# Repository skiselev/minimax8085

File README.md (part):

# MiniMax8085
Minimal 8085 Single Board Computer

## Table of Content
* [Introduction](#introduction)
* [Specifications](#specifications)
* [Hardware Documentation](#hardware-documentation)
  * [Schematic and PCB Layout](#schematic-and-pcb-layout)
  * [Design Description](#design-description)
  * [Jumpers and Connectors](#jumpers-and-connectors)
  * [Simple Programmable Logic Device](#simple-programmable-logic-device)
  * [Bill of Materials](#bill-of-materials)
* [Firmware and Software](#firmware-and-software)
  * [ROM Image](#rom-image)
  * [MON85 Monitor](#mon85-monitor)
  * [Tiny BASIC](#tiny-basic)
  * [IMSAI 8K BASIC](#imsai-8k-basic)
  * [Test Programs](#test-programs)
  * [Building the Software](#building-the-software)
* [3D Printable Enclosure](#3d-printable-enclosure)
* [Extension Boards](#extension-boards)
  * [Keypad and VFD Extension Board](#keypad-and-vfd-extension-board)
  * [Arithmetic and Extension Board](#arithmetic-and-extension-board)
* [Frequently Asked Questions and Troubleshooting](#frequently-asked-questions-and-troubleshooting)
* [References](#references)

## Introduction
The MiniMax8085 project has been brewing for almost three years. In the spring of 2014 my kids and I visited a local [surplus store](http://www.surplusgizmos.com/), where my kids found some Intel 8000 series parts in the kids-fill-your-bucket area. Among these ICs were there: an 8085 CPU, an 8155 RAM with I/O ports and timer, a couple of 8255 PPIs, an 8282 latch, and some 27C128 UV EPROMs. It looked like a good start for an 8085 based computer that can be used to teach my kids some computer design and programming basics.
I wanted the project to be simple to build, with a minimal number of components, but yet to be a fully functional single board computer (e.g. to include the memory and an input/output device, for example a UART) with an extension bus. I checked the Internet for existing homebrew 8085 computers and found Roman Fülek's [NCB85](http://archeocomp.blogspot.com/2013/01/ncb85.html) and [NCB85v2](http://archeocomp.blogspot.com/2014/01/ncb85-7-nove-ncb85v2.html) projects, and Glitch Works [8085 projects](http://www.glitchwrks.com/8085projects.html). While I liked these projects, they didn't quite meet my project design goals:
* [NCB85](http://archeocomp.blogspot.com/2013/01/ncb85.html) was the closest, but it doesn't have an extension bus
* [NCB85v2](http://archeocomp.blogspot.com/2014/01/ncb85-7-nove-ncb85v2.html) is a little bit too complicated for my needs
* [Glitch Works 8085](http://www.glitchwrks.com/8085projects.html) project didn't have an on-board UART

The resulting design includes 8085 CPU, 8251 USART, 32 KiB SRAM, 32 KiB or 16 KiB ROM. It uses a GAL16V8/ATF16V8 simple programmable logic device (SPLD) instead of discrete logic ICs for the address decode and the frequency divider for USART. It reduces the number of components, allows for tweaking the configuration by re-programming the SPLD, and provides an introduction to the programmable logic devices.

## Specifications
* 80C85A or 8085A CPU, 3.072 MHz, 4 MHz, 4.9152 MHz, 6.144 MHz, or 8 MHz CPU clock frequency
* 82C51A or 8251A USART for console connection
* 32 KiB of battery backed SRAM
* Up to 32 KiB of ROM. EEPROM, UV EPROM or Flash ROM memory is supported
* 40-pin extension bus connector, including most of 8085 signals and demultiplexed data and address buses

## Hardware Documentation

### Schematic and PCB Layout

[Schematic - Version 1.0](KiCad/Mini8085-Schematic-1.0.pdf)

[PCB Layout - Version 1.0](KiCad/Mini8085-Board-1.0.pdf)

### Design Description
The MiniMax8085 is based on the Intel 8085A CPU (U1). The 74*573 octal latch (U6) is used to demultiplex the lower 8-bit of address and data bus.
The board uses the Intel 8251A USART (U2) for serial input / output, for example for connecting a console. The MAX232A RS-232 driver/receiver (U7) is used to convert TTL logic levels to RS-232 voltage.
The 62256 32 KiB SRAM (U4) is used for the system RAM. The RAM is battery backed using the DS1210 NVRAM controller (U8).
The board supports a variety of ROM options (U3): The 28C256 EEPROM; UV EPROMs, such as 27C256 (32 KiB), 27C128 (16 KiB), and 27C64 (8 KiB); or The 29C256 Flash ROM ICs. Normally the ROM is mapped to the CPU memory beginning from the address *0x0000*, while the RAM is mapped beginning from the address *0x8000*. The ROM and RAM addresses can be swapped by pulling /SWAP_MEM signal low. This can be used, for example, to implement a CP/M extension card. 
The GAL16V8 simple programmable logic device (U5) implements all the required "glue" logic functions:
* Address decode and chip select for the USART. The default USART I/O address is *0x08*.
* Clock divider that divides the CPU clock to obtain USART transmit and receive clock. The divisor value depends on the CPU speed. Fuse maps with divide by 10 and 20, divide by 13 and 26, and divide by 16 and 32 ratios are provided to support common 8085A CPU clocks: 3.072 MHz, 4 MHz, 4.9152 MHz, 6.144 MHz, and 8 MHz.
* Address decode and chip select for the ROM and SRAM. The address decode logic include additional /SWAP_MEM input, which by default is configured to swap address mapping of ROM and RAM.

Please refer to the [Simple Programmable Logic Device](#simple-programmable-logic-device) section below for more details regarding the SPLD configuration and programming.

The MiniMax8085 includes a 40-pin extension connector (P4), that features the 8085A address and data buses, and control signals. Please refer to the Jumpers and Connectors section below for the connector pinout and signals description.

### Jumpers and Connectors

#### Jumpers JP1 and JP2 - ROM Configuration

These jumpers configure how pins 1 and 27 of the ROM IC (U3) are connected. The jumper settings are printed on the bottom side of the PCB.
ROM Type                   | Jumper JP1 Position - ROM Pin 1 Connection                        | JP2 Position - ROM Pin 27 Connection
-------------------------- | ----------------------------------------------------------------- | ------------------------------------
27C128, 27C64, 27128, 2764 | 2-3 - pin 1 connected to VCC                                      | 1-2 - pin 27 connected to VCC
27C256                     | 2-3 - pin 1 connected to VCC                                      | 2-JP1 pin 1 (jumper installed vertically), pin 27 connected to A14
28C256                     | 1-2 - pin 1 connected to A14                                      | 2-3 - pin 27 connected to /WR
29C256                     | 2-JP2 pin 3 (jumper installed vertically), pin 1 connected to /WR | 2-JP1 pin 1 (jumper installed vertically), pin 27 connected to A14

#### Jumper JP3 - USART Clock Frequency

JP3 sets the USART input clock frequency

Jumper Position | Crystal Y1 Frequency (CPU Frequency)                          | USART Clock Frequency | USART Bit rate
--------------- | ------------------------------------------------------------- | --------------------- | --------------
1-2             | 6.144 MHz (3.073 MHz), 8 MHz (4 MHz), 9.8304 MHz (4.9152 MHz) | 307.2 kHz             | 19200 bps (default) or 2400 bps, depending on USART configuration
1-2             | 12.288 MHz (6.144 MHz), 16 Mhz (8 MHz)                        | 614.4 kHz             | 38400 bps (default) or 4800 bps, depending on USART configuration
2-3             | 6.144 MHz (3.073 MHz), 8 MHz (4 MHz), 9.8304 MHz (4.9152 MHz) | 153.6 kHz             | 9600 bps (default) or 1200 bps, depending on USART configuration
2-3             | 12.288 MHz (6.144 MHz), 16 MHz (8 MHz)                        | 307.2 kHz             | 19200 bps (default) or 2400 bps, depending on USART configuration

#### Connector P1 - POWER

Connect regulated +5V power supply to this connector.
Pin                     | Description
----------------------- | -----------
tip (the inner contact) | Positive terminal - +5V
barrel / sleeve         | Negative terminal - ground

#### Connector P2 - SIO

Connector P2 contains the 8085A CPU serial input and output lines.
Pin | Description
--- | -----------
1   | Ground
2   | SOD / Serial Output Data
3   | SID / Serial Input Data

#### Connector P3 - SERIAL

P3 is the serial port connector. It is normally used for connecting a console or terminal. P3 uses pinout similar to that of IBM AT serial port (with some signals missing). Use a null modem cable to connect to a PC.

Pin Number | Signal Name       | Description and Notes
---------- | ----------------- | ---------------------
1          | DCD               | Carrier Detect; Not used - Not connected on the SBC
**2**      | **RX**            | **Receive Data; Input to SBC**
**3**      | **TX**            | **Transmit Data; Output from SBC**
4          | DTR               | Data Terminal Ready; Not used - Not connected on the SBC
**5**      | **Signal Ground** | **Connected to the SBC GND signal**
6          | DSR               | Data Set Ready; Not used - Not connected on the SBC
**7**      | **RTS**           | **Request to Send; Output from SBC**
**8**      | **CTS**           | **Clear to Send; Input to SBC**
9          | RI                | Ring Indicator; Not used - Not connected on the SBC
**Shield** | **DE9 Shield**    | **Connected to the SBC GND signal**

#### Connector P4 - EXTENSION

Connector P4 contains the 8085A CPU address and data buses, and control signals.

Pin | Signal    | Description                             | Pin | Signal | Description
--- | --------- | --------------------------------------- | --- | ------ | -----------
1   | TRAP      | Non-maskable interrupt input            | 21  | AD5    | Address/data bus - bit 5 bi-directional
2   | 3.073 MHz | CPU clock output                        | 22  | AD4    | Address/data bus - bit 4 bi-directional
3   | RST5_5    | RST5.5 interrupt input                  | 23  | AD7    | Address/data bus - bit 7 bi-directional
4   | INTR      | Interrupt request input                 | 24  | AD6    | Address/data bus - bit 6 bi-directional
5   | RST7_5    | RST7.5 interrupt input                  | 25  | /RD    | Read control output
6   | /INTA     | Interrupt acknowledge output            | 26  | IO/M   | I/O / memory cycle status output
7   | ALE	      | Address latch enable output             | 27  | /WR    | Write control output
8   | /SWAP_MEM | Swap ROM & RAM addresses input          | 28  | RESET  | Reset output
9   | A9        | Address bus - bit 9 output              | 29  | A1     | Address bus - bit 1 output
10  | A8        | Address bus - bit 8 output              | 30  | A0     | Address bus - bit 0 output
11  | A11       | Address bus - bit 11 output             | 31  | A3     | Address bus - bit 3 output
12  | A10       | Address bus - bit 10 output             | 32  | A2     | Address bus - bit 2 output
13  | A13       | Address bus - bit 13 output             | 33  | A5     | Address bus - bit 5 output
14  | A12       | Address bus - bit 12 output             | 34  | A4     | Address bus - bit 4 output
15  | A15       | Address bus - bit 15 output             | 35  | A7     | Address bus - bit 7 output
16  | A14       | Address bus - bit 14 output             | 36  | A6     | Address bus - bit 6 output
17  | AD1       | Address/data bus - bit 1 bi-directional | 37  | VCC    | Power - 5V
18  | AD0       | Address/data bus - bit 0 bi-directional | 38  | VCC    | Power - 5V
19  | AD3       | Address/data bus - bit 3 bi-directional | 39  | GND    | Power - Ground
20  | AD2       | Address/data bus - bit 2 bi-directional | 40  | GND    | Power - Ground

#### Connector P5 - VBAT

P5 is used to connect the battery for the SRAM backup. A 3-volt lithium cell, or 2-3 alkaline batteries connected in series can be used for this purpose.
Pin | Description
--- | -----------
1   | Battery voltage, 3V - 5V
2   | Ground

### Simple Programmable Logic Device

#### SPLD Files and Programming

As described above, the MiniMax8085 SBC uses a GAL16V8 simple programmable logic device (SPLD) to implement all the necessary glue logic. The SLPD sources and images (fuse maps are available [SPLD](SPLD/) folder of this GitHub repository:
* [Mini8085-3.072MHz.pld](SPLD/Mini8085-3.072MHz.pld) - SPLD source code for a system with CPU running on 3.072 MHz or 6.144 MHz clock frequency. 
  * [Mini8085-3.072MHz.jed](SPLD/Mini8085-3.072MHz.jed) - SPLD fuse map for a system with CPU running on 3.072 MHz or 6.144 MHz clock frequency
  * When used with 6.144 MHz CPU clock frequency, the USART clock will be doubled. So that it will work on 19200 bps instead of 9600 bps, or 38400 bps instead of 19200 bps, depending on [JP3 setting](#jumper-jp3---usart-clock-frequency)
* [Mini8085-3.9936MHz.pld](SPLD/Mini8085-3.9936MHz.pld) - SPLD source code for a system with CPU running on 3.9936 MHz (4 MHz) or 8 MHz clock frequency
  * [Mini8085-3.9936MHz.jed](SPLD/Mini8085-3.9936MHz.jed) - SPLD fuse map for a system with CPU running on 3.9936 MHz (4 MHz) or 8 MHz clock frequency
  * When used with 8 MHz CPU clock frequency, the USART clock will be doubled. So that it will work on 19200 bps instead of 9600 bps, or 38400 bps instead of 19200 bps, depending on [JP3 setting](#jumper-jp3---usart-clock-frequency)
* [Mini8085-4.9152MHz.pld](SPLD/Mini8085-4.9152MHz.pld) - SPLD source code for a system with CPU running on 4.9152 MHz clock frequency
  * [Mini8085-4.9152MHz.jed](SPLD/Mini8085-4.9152MHz.jed) - SPLD fuse map for a system with CPU running on 4.9152 MHz clock frequency

The SPLD IC has to be programmed using an EPROM programmer, such as a popular MiniPro TL866CS programmer. The process is very similar to programming regular EPROM ICs:
* Select IC manufacturer: Lattice for GAL16V8 or Atmel for ATF16V8
* Select the SPLD type: GAL16V8 or ATF16V8
* Load the SPLD fuse map - pick one of [Mini8085-3.072MHz.jed](SPLD/Mini8085-3.072MHz.jed), [Mini8085-3.9936MHz.jed](SPLD/Mini8085-3.9936MHz.jed), or [Mini8085-4.9152MHz.jed](SPLD/Mini8085-4.9152MHz.jed) files, depending on the CPU frequency (or the crystal resonator you are using).
* Program the SPLD. You might want to disable "lock" option, so that SPLD will remain readable after the programming.

#### SPLD Implementation
The [Mini8085-3.072MHz.pld](SPLD/Mini8085-3.072MHz.pld), [Mini8085-3.9936MHz.pld](SPLD/Mini8085-3.9936MHz.pld), and [Mini8085-4.9152MHz.pld](SPLD/Mini8085-4.9152MHz.pld) files contain the SPLD source code, that describes the logic equations defining the desired SPLD functionality. The source code can be divided into the following sections:

##### Header
This part contains the name of the SPLD and the project name:
<pre><code>
GAL16V8       ; 8085 SBC Logic first line : used GAL
8085Mini      ;                second line: any text (max. 8 char.)
</code></pre>

##### Pin Names Definition
This part assigns names to the SPLD pins. The names order corresponds to the pin numbers: the first line assigns names to the pins 1 - 10, and the second line to the pins 11 - 20. Note that several pins have fixed functions: pin 1 - Clock, pin 10 - GND, pin 11 - /OE, and pin 20 - VCC. Also pins 2 - 9 can be used as inputs only, while pins 12 - 19 can be used as either inputs or outputs.
<pre><code>
Clock IOM    A15    SWAPMEM A7    A6    A5    A4    A3   GND
/OE   RAMCS  ROMCS  USARTCS Q4    Q3    Q2    Q1    Q0   VCC
</code></pre>

##### Logic Equations - USART Clock Frequency Divider
The frequency divider is implemented as a synchronous counter, where all the outputs change their state simultaneously with the rising edge of the Clock signal. To achieve this, the SPLD is configured in *registered* mode (this is done automatically, by the SPLD assembler). In this mode the SPLD outputs with .R suffix (Q0.R - Q4.R) are configured as D flip-flops, and their logic equations describe the next state of the flip-flops (the values on their D inputs, that will be latched with the Clock signal). For example, in [Mini8085-4.9152MHz.pld](SPLD/Mini8085-4.9152MHz.pld) the next state of Q0 output is defined to be the inverse of its current state: Q0.R = /Q0. The Q0 - Q2 outputs are the outputs of intermediate stages of counter/divider, and they are not used in the MiniMax8085. The USART clock inputs are connected to either Q3 or Q4 output, depending on the position of the jumper JP3, resulting in divide by either 10 or 20 for 3.072 MHz CPU clock (using the [Mini8085-3.072MHz.pld](SPLD/Mini8085-3.072MHz.pld) fuse map), divide by either 13 or 26 for 4.9152 MHz CPU clock (using the [Mini8085-3.9936MHz.pld](SPLD/Mini8085-3.9936MHz.pld) fuse map), or divide by either 16 or 32 for 4.9152 MHz CPU clock (using the [Mini8085-4.9152MHz.pld](SPLD/Mini8085-4.9152MHz.pld) fuse map).

[Mini8085-4.9152MHz.pld](SPLD/Mini8085-4.9152MHz.pld): 5-bit binary counter, or divide by 32 frequency divider.
<pre><code>
Q0.R =   /Q0
 
Q1.R =    Q1 * /Q0
       + /Q1 *  Q0

Q2.R =    Q2 * /Q1
       +  Q2 * /Q0
       + /Q2 *  Q1 *  Q0

Q3.R =    Q3 * /Q2
       +  Q3 * /Q1
       +  Q3 * /Q0
       + /Q3 *  Q2 *  Q1 *  Q0

Q4.R =    Q4 * /Q3
       +  Q4 * /Q2
       +  Q4 * /Q1
       +  Q4 * /Q0
       + /Q4 *  Q3 *  Q2 *  Q1 *  Q0
</code></pre>

[Mini8085-3.072MHz.pld](SPLD/Mini8085-3.072MHz.pld): Q2-Q0 implement divide by 5 frequency divider, Q3 and Q4 stages divide the frequency further by 2 and 4 respectively.
<pre><code>
Q0.R =   /Q2 * /Q0

Q1.R =   /Q2 * /Q1 *  Q0
       + /Q2 *  Q1 * /Q0

Q2.R =   /Q2 *  Q1 *  Q0

Q3.R =    Q3 * /Q2
       + /Q3 *  Q2

Q4.R =    Q4 * /Q3
       +  Q4 * /Q2
       + /Q4 *  Q3 *  Q2
</code></pre>

#### Logic Equations - Memory Chip Select
These equations activate /ROMCS and /RAMCS signals:
The /ROMCS is active (LOW) when 8085 IO/M signal is LOW, indicating a memory access, and either A15 is LOW (lower 32 KiB of memory address space) and SWAPMEM is inactive (HIGH), or then A15 is HIGH (upper 32 KiB of memory address space), and SWAPMEM is active (LOW).
The /RAMCS is active (LOW) when 8085 IO/M is LOW, indicating a memory access, and either A15 is HIGH (upper 32 KiB of memory address space) and SWAPMEM is inactive (HIGH), or then A15 is LOW (lower 32 KiB of memory address space), and SWAPMEM is active (LOW).

<pre><code>
/ROMCS =   /IOM *  SWAPMEM * /A15
         + /IOM * /SWAPMEM *  A15

/RAMCS =   /IOM *  SWAPMEM *  A15
         + /IOM * /SWAPMEM * /A15
</code></pre>

#### Logic Equations - USART Chip Select
This equation activates the /USARTCS signal. It is active (LOW) when 8085 IO/M signal is HIGH, indicating an I/O port access, address lines A7-A4 are LOW, and address line A3 is high. So that USART is selected using  00001xxxb addresses (8h-0Fh).

<pre><code>
/USARTCS = IOM * /A7 * /A6 * /A5 * /A4 * A3
</code></pre>

### Bill of Materials

[MiniMax8085 project on Mouser.com](http://www.mouser.com/ProjectManager/ProjectDetail.aspx?AccessID=e60fdda470) - View and order all components except of the 8085A CPU, the 8251A USART, and the PCB.

[MiniMax8085 project on OSHPark.com](https://www.oshpark.com/shared_projects/CyQsELdX) - View and order the MiniMax8085 PCB.

Component Type | Reference | Description                               | Quantity | Possible Sources and Notes
-------------- | --------- | ----------------------------------------- | -------- | --------------------------
PCB            |           | MiniMax8085 PCB Version 1.0               | 1        | OSH Park [MiniMax 8085 V1.0](https://www.oshpark.com/shared_projects/CyQsELdX)
Capacitor      | C1 - C11  | 0.1 uF ceramic, 5.08 mm lead spacing      | 11       | Mouser [594-K104K15X7RF53H5](https://www.mouser.com/ProductDetail/594-K104K15X7RF53H5), [810-FG28X7R1H104KNT6](https://www.mouser.com/ProductDetail/810-FG28X7R1H104KNT6); Jameco [15270](https://www.jameco.com/z/DC-1-50-7-Jameco-Valuepro-Capacitor-Ceramic-Disc-0-1-micro-F-50V-plusmn-20-_15270.html)
Capacitor      | C12       | 1 uF ceramic, 5.08 mm lead spacing        | 1        | Mouser [810-FG28X7R1E105KRT6](https://www.mouser.com/ProductDetail/810-FG28X7R1E105KRT6)
Capacitor      | C13       | 10 uF ceramic, 5.08 mm lead spacing       | 1        | Mouser [810-FG28X5R1E106MR00](https://www.mouser.com/ProductDetail/810-FG28X5R1E106MR00). Note: Can be replaced with tantalum or electrolytic capacitors
Capacitor      | C14, C15  | 33 pF ceramic, 5.08 mm lead spacing       | 2        | Mouser [75-1C20C0G330J050B](https://www.mouser.com/ProductDetail/75-1C20C0G330J050B); Jameco [332217](https://www.jameco.com/z/DC33-50-Jameco-Valuepro-Capacitor-Ceramic-Disc-33pF-50V-plusmn20-37_332217.html).Note: Install only when using CMOS 80C85A CPU. Do not install when using NMOS 8085A
Connector      | P1        | DC jack                                   | 1        | Mouser [806-KLDX-0202-A](https://www.mouser.com/ProductDetail/806-KLDX-0202-A); Jameco [101179](https://www.jameco.com/z/GCD014-R-Jameco-Valuepro-2-1mm-Male-DC-Power-Jack-Solder-Eyelet-Terminals_101179.html), [101178](https://www.jameco.com/z/GCD014-Jameco-Valuepro-2-1mm-DC-Power-Jack-Male-Solder-Eyelet-Panel-Mount-Groove-_101178.html)
Connector      | P2, JP1 - JP3 | 3x1 pin header                        | 4        | Mouser [855-M20-9990345](https://www.mouser.com/ProductDetail/855-M20-9990345), [649-69190-103HLF](https://www.mouser.com/ProductDetail/649-69190-103HLF), [649-78229-103HLF](https://www.mouser.com/ProductDetail/649-78229-103HLF); Jameco [109576](https://www.jameco.com/z/7000-1X3SG-R-Jameco-Valuepro-Header-1-Straight-Male-1-Row-3-Pin-10-025-Post-23-Goldtail_109576.html)
Connector      | P3        | DE9M, right angle PCB mount               | 1        | Mouser [806-K22X-E9P-N-99](https://www.mouser.com/ProductDetail/806-K22X-E9P-N-99) (teal color), [806-K22X-E9P-N](https://www.mouser.com/ProductDetail/806-K22X-E9P-N); Jameco [104943](https://www.jameco.com/z/1008-9P-R-Jameco-Valuepro-Connector-D-Subminiature-Male-9-Position-2-77mm-Solder-Right-Angle-Through-Hole-9-Terminal-1-Port_104943.html), [614459](https://www.jameco.com/z/747840-6-TE-Connectivity-Connector-D-Subminiature-Plug-9-Position-2-74mm-Solder-Right-Angle-Through-Hole-9-Terminal-1-Port-Tray_614459.html), [614432](https://www.jameco.com/z/5747840-3-TE-Connectivity-Connector-D-Subminiature-Plug-9-Position-2-74mm-Solder-Right-Angle-Through-Hole-9-Terminal-1-Port_960837.html)
Connector      | P4        | 20x2 pin socket                           | 1        | Mouser [517-929852-01-20-RB](https://www.mouser.com/ProductDetail/517-929852-01-20-RB). Note: Optional, used for extension bus
Connector      | P5        | 2 pin header with friction lock           | 1        | Mouser [571-6404562](https://www.mouser.com/ProductDetail/571-6404562), [571-3-641126-2](https://www.mouser.com/ProductDetail/571-3-641126-2), [571-3-641215-2](https://www.mouser.com/ProductDetail/571-3-641215-2); Jameco [232266](https://www.jameco.com/z/22-23-2021-Molex-Connector-Wire-to-Board-Header-2-Position-2-54mm-Solder-Straight-Thru-Hole-Color-may-vary-_232266.html), [613931](https://www.jameco.com/z/640456-2-TE-Connectivity-Connector-Wire-to-Board-Header-2-Position-2-54mm-Solder-Straight-Thru-Hole_613931.html). Note: Optional, used for SRAM battery backup. Corresponding female connector: Mouser [571-13758202](https://www.mouser.com/ProductDetail/571-13758202); Jameco [234798](https://www.jameco.com/z/22-01-3027-Molex-Straight-Connector-Housing-Receptacle-2-Position-2-54mm-Color-may-vary-_234798.html). Contacts (2 contacts needed): Mouser [571-14453361](https://www.mouser.com/ProductDetail/571-14453361); Jameco [234923](https://www.jameco.com/z/08-50-0114-Molex-0-100-2-54mm-Connector-Contact-Female-1-Position-Crimp-Straight-Cable-Mount-Bag_234923.html), [736501](https://www.jameco.com/z/08-50-0113-Molex-Connector-Contact-Female-1-Position-Crimp-Straight-Cable-Mount-Reel_736501.html).  It is recommended to use a polarized header to avoid incorrect power polarity.
Diode          | D1        | 1N4148                                    | 1        | Mouser [512-1N4148TR](https://www.mouser.com/ProductDetail/512-1N4148TR), [512-1N4148](https://www.mouser.com/ProductDetail/512-1N4148), [78-1N4148](https://www.mouser.com/ProductDetail/78-1N4148); Jameco [36038](https://www.jameco.com/z/1N4148-Major-Brands-Diode-1N4148-100V-200mA-10mA-If-Small-Signal-Switching-Bulk-_36038.html), [179215](https://www.jameco.com/z/1N4148-Major-Brands-Diode-1N4148-100V-200mA-10mA-If-Small-Signal-Switching-Bulk-_36038.html)
LED            | D2        | LED Indicator, Dialight 566-0206F         | 1        | Mouser [645-566-0206F](https://www.mouser.com/ProductDetail/645-566-0206F).  Note: Can be replaced with a standard 3 mm or 5 mm LED
Resistor       | R1        | 33 Ohm, 1/4 W                             | 1        | Mouser [240-CFR-25JT-52-33R](https://www.mouser.com/ProductDetail/240-CFR-25JT-52-33R); Jameco [690507](https://www.jameco.com/z/CF1-4W330JRC-Jameco-Valuepro-Resistor-Carbon-Film-33-Ohm-5-1-4-Watt_690507.html)
Resistor       | R2        | 470 Ohm, 1/4 W                            | 1        | Mouser [603-CFR-25JT-52-470R](https://www.mouser.com/ProductDetail/603-CFR-25JT-52-470R); Jameco [690785](https://www.jameco.com/z/CF1-4W471JRC-Jameco-Valuepro-Resistor-Carbon-Film-470-Ohm-1-4-Watt-5-_690785.html)
Resistor       | R3        | 100 kOhm, 1/4 W                           | 1        | Mouser [603-CFR-25JT-52-100K](https://www.mouser.com/ProductDetail/603-CFR-25JT-52-100K); Jameco [691340](https://www.jameco.com/z/CF1-4W104JRC-Jameco-Valuepro-Resistor-Carbon-Film-100k-Ohm-1-4-Watt-5-_691340.html)
Resistor Array | RR1, RR2  | 4.7 kOhm, 6 pin, bussed resistor array    | 2        | Mouser [264-4.7K-RC](https://www.mouser.com/ProductDetail/264-4.7K-RC), [652-4606X-1LF-4.7K](https://www.mouser.com/ProductDetail/652-4606X-1LF-4.7K)
Switch         | SW1       | Tactile switch, right angle               | 1        | Mouser [653-B3F-3100](https://www.mouser.com/ProductDetail/653-B3F-3100), [653-B3F-3152](https://www.mouser.com/ProductDetail/653-B3F-3152), [706-95C06A2RAT](https://www.mouser.com/ProductDetail/706-95C06A2RAT), [706-95C06C2RAT](https://www.mouser.com/ProductDetail/706-95C06C2RAT), [706-95C06F2RAT](https://www.mouser.com/ProductDetail/706-95C06F2RAT); Jameco [2280495](https://www.jameco.com/z/SKHHLNA010-Alps-Electric-SPST-NO-OFF-MOM-Tactile-Switch-12VDC-50mA_2280495.html). Note: Switches can have different actuator length. You might want to select the switch according your own preferences, for example the enclosure type you want to use, and whatever you want the reset button to stick out of the enclosure or to stay hidden inside.
Crystal        | Y1        | 6.144 MHz quartz resonator for 3 MHz CPU; 8 MHz quartz resonator for 4 MHz CPU; 9.8304 MHz quartz resonator for 5 MHz CPU; 12.288 MHz quartz resonator for 6 MHz CPU ; 16 MHz quartz resonator for 8 MHz CPU | 1 | Mouser [520-61-18-4XEN](https://www.mouser.com/ProductDetail/520-61-18-4XEN) (6.144 MHz), [695-HC49US-983-U](https://www.mouser.com/ProductDetail/695-HC49US-983-U) (9.8304 MHz), [695-HC49US-122-U](https://www.mouser.com/ProductDetail/695-HC49US-122-U) (12.288 MHz), [815-ABL-16-B2](https://www.mouser.com/ProductDetail/815-ABL-16-B2) (16 MHz); Unicorn Electronics 6.144 MHz or 9.8304 MHz according to desired CPU clock frequency.
IC             | U1        | 80C85A, 8085A-2, or 8085A CPU             | 1        | Jameco [8085A-2, 5 MHz - 52071](https://www.jameco.com/z/8085A-2-Major-Brands-IC-8085A-2-8-Bit-CPU-32-I-O-5MHz-DIP-40-pin_52071.html), [8085A, 3 MHz - 52062](https://www.jameco.com/z/8085A-Major-Brands-IC-8085A-8-Bit-HMOS-MPU_52062.html); Unicorn Electronics 80C85, 8085A-2, or 8085A; eBay (search for 80C85 or 8085 CPUs, or IM1821VM85A / ИМ1821ВМ85А for Soviet 80C85 clone).  Note: Use CMOS part - 80C85A for lower power consumption
IC             | U2        | 82C51A, or 8251A USART                    | 1        | Jameco [8251A - 52652](https://www.jameco.com/z/8251A-Major-Brands-IC-8251A-USART-28-pin-DIP_52652.html) [82C51A - 52370](https://www.jameco.com/z/82C51A-Major-Brands-IC-82C51A-USART-CMOS-Transceiver-28-pin-DIP_52370.html), [NEC D8251AC - 52644](https://www.jameco.com/z/D8251AC-NEC-Corporation-IC-USART-8251-Dip-28_52644.html); Unicorn Electronics 82C51 or 8051; eBay (search for 82C51 or 8251 USART, or 580VV51 / 580ВВ51 for Soviet 8251 clone).  Note: Use CMOS part - 82C51A for lower power consumption
IC             | U3        | 28C256 EEPROM, 27C256 UV EPROM, 27C128 UV EPROM, 27128 UV EPROM, 27C64 UV EPROM, 2764 UV EPROM | 1 | Mouser [556-AT28C25615PU](https://www.mouser.com/ProductDetail/556-AT28C25615PU); Jameco [28C256 EEPROM - 74843](https://www.jameco.com/z/28C256-15-Major-Brands-IC-28C256-15-EEPROM-256K-Bit-CMOS-Parallel_74843.html), [27C256 UV EPROM - 39714](https://www.jameco.com/z/27C256-15-Major-Brands-IC-27C256-15-EPROM-256K-Bit-150ns-CMOS-UV-Erasable-Prommable-ROM_39714.html); Unicorn Electronics 28C256-15 (EEPROM), 27C256 or 27C128 (UV EPROM). Note: EEPROM parts are recommended. UV lamp is required to erase UV EPROMs
IC             | U4        | 62256 SRAM                                | 1        | Mouser [913-AS6C62256-55PCN](https://www.mouser.com/ProductDetail/913-AS6C62256-55PCN); Jameco [CY62256LL-70PC - 391822](https://www.jameco.com/z/CY62256LL-70PC-Cypress-Semiconductor-IC-CY62256LL-70PC-CMOS-SRAM-256k-Bit-32kx8-Asynch-70ns-Low-Power_391822.html), [CY62256L-70PC - 391793](https://www.jameco.com/z/CY62256L-70PC-Cypress-Semiconductor-IC-CY62256L-70PC-CMOS-SRAM-256K-Bit-32kx8-55-70ns-Low-Power_391793.html), [62256LP-70 - 82472](https://www.jameco.com/z/62256LP-70-Major-Brands-IC-62256LP-CMOS-SRAM-256K-Bit-32Kx8-70ns-Low-Power_82472.html), [62256LP-10 - 42833](https://www.jameco.com/z/62256LP-10-Major-Brands-Static-RAM-32K-x-8-Bit-High-Speed-CMOS-100ns-DIP-28_42833.html), [62256LP-15 - 42850](https://www.jameco.com/z/62256LP-15-Major-Brands-Static-RAM-32K-x-8-Bit-High-Speed-CMOS-150ns-DIP-28_42850.html); Unicorn Electronics 62256LP-70 (or any other 62256)
IC             | U5        | GAL16V8, ATF16V8                          | 1        | Mouser [556-AF16V8B15PU](https://www.mouser.com/ProductDetail/556-AF16V8B15PU), Jameco [GAL16V8D-15LP - 2290551](https://www.jameco.com/z/GAL16V8D-15LP-Lattice-Semiconductor-Corporation-IC-16V8D-15-High-Performance-EE-CMOS-PLD-Generic-Array-Logic-15ns-90mA-250MHz_2290551.html), [GAL16V8D-25LP - 876539](https://www.jameco.com/z/GAL16V8D-25LP-Lattice-Semiconductor-Corporation-IC-GAL16V8D-25-EECMOS-64x32-GAL-41-6MHz-20-pin-DIP_876539.html); Unicorn Electronics 16V8 (10 ns, 12 ns, or 15 ns versions would work. Make sure to contact the seller and ask specifically for Lattice GAL16V8 part. iCT PEEL16V8 parts are not supported by MiniPro TL866CS programmer)
IC             | U6        | 74HCT573, 74ALS573, 74F573                | 1        | Mouser [595-SN74HCT573N](https://www.mouser.com/ProductDetail/595-SN74HCT573N), [595-SN74AHCT573N](https://www.mouser.com/ProductDetail/595-SN74AHCT573N), [595-SN74F573N](https://www.mouser.com/ProductDetail/595-SN74F573N), [595-SN74ALS573CN](https://www.mouser.com/ProductDetail/595-SN74ALS573CN); Jameco [74HCT573 - 45090](https://www.jameco.com/z/74HCT573-Major-Brands-IC-74HCT573-Tri-State-Octal-D-type-Transparent-Latch_45090.html); Unicorn Electronics 74HCT573, 74F573, 74ALS573; eBay (search for 74HCT573, 74ALS573, 74F573, or KR1533IR33 / КР1533ИР33 for Soviet 74ALS573 clone)
IC             | U7        | MAX202,  MAX232A                          | 1        | Mouser [595-TRS202ECN](https://www.mouser.com/ProductDetail/595-TRS202ECN), [700-MAX202CPE](https://www.mouser.com/ProductDetail/700-MAX202CPE), [700-MAX232ACPE](https://www.mouser.com/ProductDetail/700-MAX232ACPE); Jameco [MAX202CPE - 142535](https://www.jameco.com/z/MAX202CPE-Major-Brands-IC-MAX202CPE-RS-232-Line-Transceiver-16-pin-DIP_142535.html); Unicorn Electronics MAX202
IC             | U8        | Maxim DS1210, or Maxim MXD1210            | 1        | Mouser [700-MXD1210CPA](https://www.mouser.com/ProductDetail/700-MXD1210CPA); Jameco [DS1210 - 114198](https://www.jameco.com/z/DS1210-Dallas-Semiconductor-IC-DS1210-Nonvolatile-Controller-8-pin-DIP_114198.html); Unicorn Electronics DS1210. Note: Optional, used for SRAM battery backup. If not populated - install two wire jumpers instead as shown on the PCB silk screen
IC Socket      | U1        | 40 pin 600 mil DIP socket                 | 1        | Mouser [517-4840-6000-CP](https://www.mouser.com/ProductDetail/517-4840-6000-CP), [649-DILB40P223TLF](https://www.mouser.com/ProductDetail/649-DILB40P223TLF); Jameco [41111](https://www.jameco.com/z/6000-40DW-R-Jameco-Valuepro-40-Pin-Dual-Wipe-Low-Profile-IC-Socket-0-60-Inch-Wide_112311.html)
IC Socket      | U2 - U4   | 28 pin 600 mil DIP socket                 | 3        | Mouser [517-4828-6000-CP](https://www.mouser.com/ProductDetail/517-4828-6000-CP), [649-DILB28P223TLF](https://www.mouser.com/ProductDetail/649-DILB28P223TLF); Jameco [40301](https://www.jameco.com/z/28LPD-6-Jameco-Valuepro-28-Pin-Dual-Wipe-Low-Profile-IC-Socket-0-6-Inch-Wide_40301.html)
IC Socket      | U5, U6    | 20 pin 300 mil DIP socket                 | 2        | Mouser [517-4820-3000-CP](https://www.mouser.com/ProductDetail/517-4820-3000-CP), [649-DILB20P-223TLF](https://www.mouser.com/ProductDetail/649-DILB20P-223TLF); Jameco [38608](https://www.jameco.com/z/20LPD-Major-Brands-20-Pin-0-3-Inch-Wide-Low-Profile-Dual-Wipe-IC-Socket_112248.html)
IC Socket      | U7        | 16 pin 300 mil DIP socket                 | 1        | Mouser [517-4816-3000-CP](https://www.mouser.com/ProductDetail/517-4816-3000-CP), [649-DILB16P-223TLF](https://www.mouser.com/ProductDetail/649-DILB16P-223TLF); Jameco [37373](https://www.jameco.com/z/ICS-316-T-Jameco-Valuepro-IC-Socket-16-Pin-Dual-Wipe-Low-Profile-0-3-Inch-Wide_112222.html)
IC Socket      | U8        | 8 pin 300 mil DIP socket                  | 1        | Mouser [517-4808-3000-CP](https://www.mouser.com/ProductDetail/517-4808-3000-CP), [649-DILB8P223TLF](https://www.mouser.com/ProductDetail/649-DILB8P223TLF); Jameco [112206](https://www.jameco.com/z/8LPD-Jameco-Valuepro-8-Pin-IC-Socket-Dual-Wipe-Low-Profile-0-30-Inch-Wide_112206.html)

#### Replacement Notes

* CMOS parts are preferred for lower power consumption.
* 80C85 (CPU) - Any type in DIP-40 package will do. Use 6.144 MHz crystal for 3 MHz parts. Such parts usually don't have any numeric suffix in the part name. For example Intel P8085AH is a 3 MHz part, while Intel P8085AH-2 is a 5 MHz part.
  * CMOS parts: MSM80C85A or M80C85A (OKI), CA80C85B (Calmos, Tundra), IM1821VM85A (Soviet/Russian Clone)
  * NMOS parts: P8085A (Intel, AMD), P8085AH, P8085AH-2, P8085AH-1 (Intel, newer HMOS process, 3 MHz, 5 MHz, and 6 MHz parts respectively), M5L8085AP (Mitsubishi), TMP8085AP (Toshiba), and so on.
* 80C51A (USART) - Any type in DIP-28 package.
* 28C256 (EEPROM, EPROM) - The board support a wide variety of ROMs. Note that JP1 and JP2 jumpers need to be set according to the ROM type.
  * 28C256 EEPROM: Atmel/Microchip AT28C256, Xicor X28C256
  * CMOS UV EPROMs: 27C256 UV EPROMs (32 KiB), 27C128 UV EPROMs (16 KiB), 27C64 UV EPROMs (8 KiB)
  * NMOS UV EPROMs: 27256 UV EPROMs (32 KiB), 27128 UV EPROMs (16 KiB), 2764 UV EPROMs (8 KiB)
  * 62256-like NVRAM (32 KiB)
  * AT29C256 Flash ROM
* 62256 (SRAM) - A low-power CMOS SRAM 32KiB, in DIP-28 wide (600 mils) packages. Here are some common parts:
  * In production: AS6C62256 (Alliance Memory), CY62256N (Cypress)
  * Old stock: HM62256LP (Hitachi), HY62256 (Hyundai), KM62256 (Samsung), UM62256 (UMC)
* GAL16V8 (SPLD): Needs to be in DIP-20 package
  * In production:  Atmel/Microchip ATF16V8
  * Old stock: Lattice GAL16V8 (any modification)
  * iCT PEEL16V8 might work, but it is not supported by common MiniPro TL866CS programmer
* 74HC573 (Octal D Latch with 3-STATE Outputs) - Can be replaced with any 74-series family that works with 5V power supply voltage. 
  * CMOS parts: 74HC573, 74ACT573, 74HCT573, 74AHCT573, 74AC573, 74ACT573
  * TTL parts: 74ALS573, 74F573, 74LS573
* MAX232A (RS-232 Drivers/Receivers) - There is a variety of compatible ICs available from various manufacturers. Note that the original MAX232 part as well as some compatible ICs require 1 uF capacitors for charge pumps (C7-C11).
  * Maxim: MAX232A, MAX202, MAX232
  * Texas Instruments: TRS202, MAX232
  * Exar: SP232
  * Analog Devices: ADM202, ADM232
  * Intersil: HIN202, HIN232
* LED D2 - Can be replaced by a 3 mm LED with pins bent at 90 degrees.

## Firmware and Software

### ROM Image

The pre-built [ROM image](software/mon85-tinybasic-8kbasic.bin) for MiniMax8085 containing, the MON85 monitor, Tiny BASIC, and IMSAI 8K BASIC is provided in this repository.
This ROM image has the following layout:
* 0x0000 - 0x0FFF - MON85 Monitor. It will run automatically upon power-on or reset
* 0x1000 - 0x17FF - Tiny BASIC. Use MON85 **G 1000** command to run it
* 0x1800 - 0x3FFF - IMSAI 8K BASIC. Use MON85 **G 1800** command to run it
The image size is 8 KiB, and it will work with either 16 KiB EPROMs (e.g. 27128), and 32 KiB EPROMs. It can be programmed into 8 KiB EPROM, leaving out the IMSAI 8K BASIC.

### MON85 Monitor

MiniMax8085 uses MON85 Software Debug Monitor For the 8085/8080 written by Dave Dunfield. Specifically it was tested with the improved by Roman Borik [version 1.2](http://blog.borik.net/2012/01/upraveny-monitor-pre-ncb85.html). This version adds support for undocumented 8085 instructions and flags.

#### Usage Notes
* Use *?* command to get a short summary of the MON85 commands
* Press *ESC* button to interrupt currently running command and return to the command prompt
* Addresses and data are typed in hexadecimal, without any preferences. For example *M 18F0*

#### Files

* [MON85 source code modified for MiniMax8085](software/mon85/mon85-mini85.asm)
* [MON85 V1.2 source](software/mon85/mon85-v12-ncb85.asm)
* [MON85 Documentation](software/mon85/mon85.txt)

### Tiny BASIC

The famous [Tiny BASIC](https://en.wikipedia.org/wiki/Tiny_BASIC) 2.0 written by Li-Chen Wang and modified by Roger Rauskolb, runs on MiniMax8085 with very little modifications: The 8251 USART I/O address needs to be updated, and its initialization parameters need to be slightly updated to use 1 stop bit instead of two, and to enable CTS/RTS flow control. Also the RAM addresses need to be updated to start from 8000h.

#### Files

* [Tiny BASIC source code modified for MiniMax8085](software/tinybasic/tinybasic-2.0-mini85.asm)
* [Tiny BASIC source code modified for AS Macro Assembler](software/tinybasic/tinybasic-2.0.asm)
* [Tiny BASIC article - Interface Age Magazine, December 1976](software/tinybasic/TinyBASIC-2.0.pdf)

### IMSAI 8K BASIC

IMSAI 8K BASIC runs on MiniMax8085 with minimal modifications (memory and USART I/O addresses), and provides floating point support. With that being said, it is slower that Tiny BASIC.

#### Usage Notes
* The operators and commands must be typed in upper case
* After power-on, make sure to type *NEW* command before typing any other commands
* The BASIC program in memory is preserved across reboots

#### Files

* [IMSAI 8K BASIC source code modified for MiniMax8085](software/8kbasic/8kbasic-mini85.asm)
* [IMSAI 8K BASIC source code modified for AS Macro Assembler](software/8kbasic/8kbasic.asm)
* [IMSAI 8K BASIC Documentation](software/8kbasic/imsai_8k_basic.pdf)

### Test Programs

#### Minimal Test Code - Blink an LED 

The code below blinks an LED connected to 8085's SOD output.
The code is borrowed from [Glitch Works 8085 SBC project](http://www.glitchwrks.com/2010/09/02/8085-sbc)

<pre><code>
;Assembly                                 Address    Opcode

;Flash a LED on SOD

;Load C000h to SP
START:          LXI     H,0C000h        ; 0000       21 00 C0
                SPHL                    ; 0003       F9

FLASH:          MVI     A,0C0h          ; 0004       3E C0
                SIM                     ; 0006       30
                CALL    DELAY           ; 0007       CD 13 00
                MVI     A,40h           ; 000A       3E 40
                SIM                     ; 000C       30
                CALL    DELAY           ; 000D       CD 13 00
                JMP     FLASH           ; 0010       C3 04 00

;Delay, return to HL when done.
DELAY:          MVI     A, 0FFh         ; 0013       3E FF
                MOV     B,A             ; 0015       47
PT1:            DCR     A               ; 0016       3D
PT2:            DCR     B               ; 0017       05
                JNZ     PT2             ; 0018       C2 17 00
                CPI     00h             ; 001B       FE 00
                JNZ     PT1             ; 001D       C2 16 00
                RET                     ; 0020       C9
</code></pre>

#### USART Test Code
This code prints "8085" to the serial port, and then echoes received characters.

<pre><code>
; USART registers
USART_DATA     EQU     08h
USART_CMD      EQU     09h

START:         LXI     H,0C000h
               SPHL
               CALL    USART_INIT

; write a banner
               MVI     A,38h           ; '8'
               MOV     C,A
               CALL    USART_OUT
               MVI     A,30h           ; '0'
               MOV     C,A
               CALL    USART_OUT
               MVI     A,38h           ; '8'
               MOV     C,A
               CALL    USART_OUT
               MVI     A,35h           ; '5'
               MOV     C,A
               CALL    USART_OUT
               MVI     A,0Dh           ; CR
               MOV     C,A
               CALL    USART_OUT
               MVI     A,0Ah           ; LF
               MOV     C,A
               CALL    USART_OUT

LOOP:
               CALL    USART_IN
               MOV     C,A
               CALL    USART_OUT
               JMP     LOOP

USART_INIT:    MVI     A,00h
; Set USART to command mode - configure sync operation, write two dummy sync characters
               OUT     USART_CMD
               OUT     USART_CMD
               OUT     USART_CMD
; Issue reset command
               MVI     A,40h
               OUT     USART_CMD
; Write mode instruction - 1 stop bit, no parity, 8 bits, divide clock by 16
               MVI     A,4Eh
               OUT     USART_CMD
; Write command instruction - activate RTS, reset error flags, enable RX, activate DTR, enable TX
               MVI     A,37h
               OUT     USART_CMD
; Clear the data register
               IN      USART_DATA
               RET

; Read character from USART
USART_IN:      IN      USART_CMD       ; Read USART status
               ANI     2               ; Test RxRdy bit
               JZ      USART_IN        ; Wait for the data
               IN      USART_DATA      ; Read character
               RET

; Write character to USART
USART_OUT:     IN      USART_CMD
               ANI     1               ; Test TxRdy
               JZ      USART_OUT       ; Wait until USART is ready to transmit
               MOV     A,C
               OUT     USART_DATA      ; Write character
               RET
</code></pre>

#### Files
* [test_usart_echo.asm](software/tests/test_usart_echo.asm)

### Building the Software

The provided source code can be built using the [AS macroassembler](http://john.ccac.rwth-aachen.de:8000/as/)
Here are steps to compile the code, assuming Windows host, and that AS installed in *C:\asw\* folder:
* Build: **c:\asw\bin\asw.exe -L -cpu 8085 *filename.asm***
  * *-L* generates listing and writes it to *filename.lst*
  * *-cpu 8085* - specifies CPU type
  * Output: *filename.p*
* Generate binary image: **c:\asw\bin\p2bin *filename***
  * Input: *filename.p*
  * Output: *filename.bin*
* Generate Intel HEX: **c:\asw\bin\p2hex -l 32 *filename***
  * *-l 32* - line length - 32 bytes (default 16 bytes)
  * Input: *filename.p*
  * Output: *filename.hex*

## 3D Printable Enclosure

See [3D Printable Enclosure for MiniMax8085](printed_parts/README.md) page for the instructions, STL files, OpenSCAD source.

## Extension Boards

### Keypad and VFD Extension Board

The [Keypad and VFD (vacuum fluorescent display) extension board](https://github.com/skiselev/minimax8085-keypad-vfd) provides simple 20-key keypad and display for MiniMax8085 SBC.

### Arithmetic and Extension Board

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
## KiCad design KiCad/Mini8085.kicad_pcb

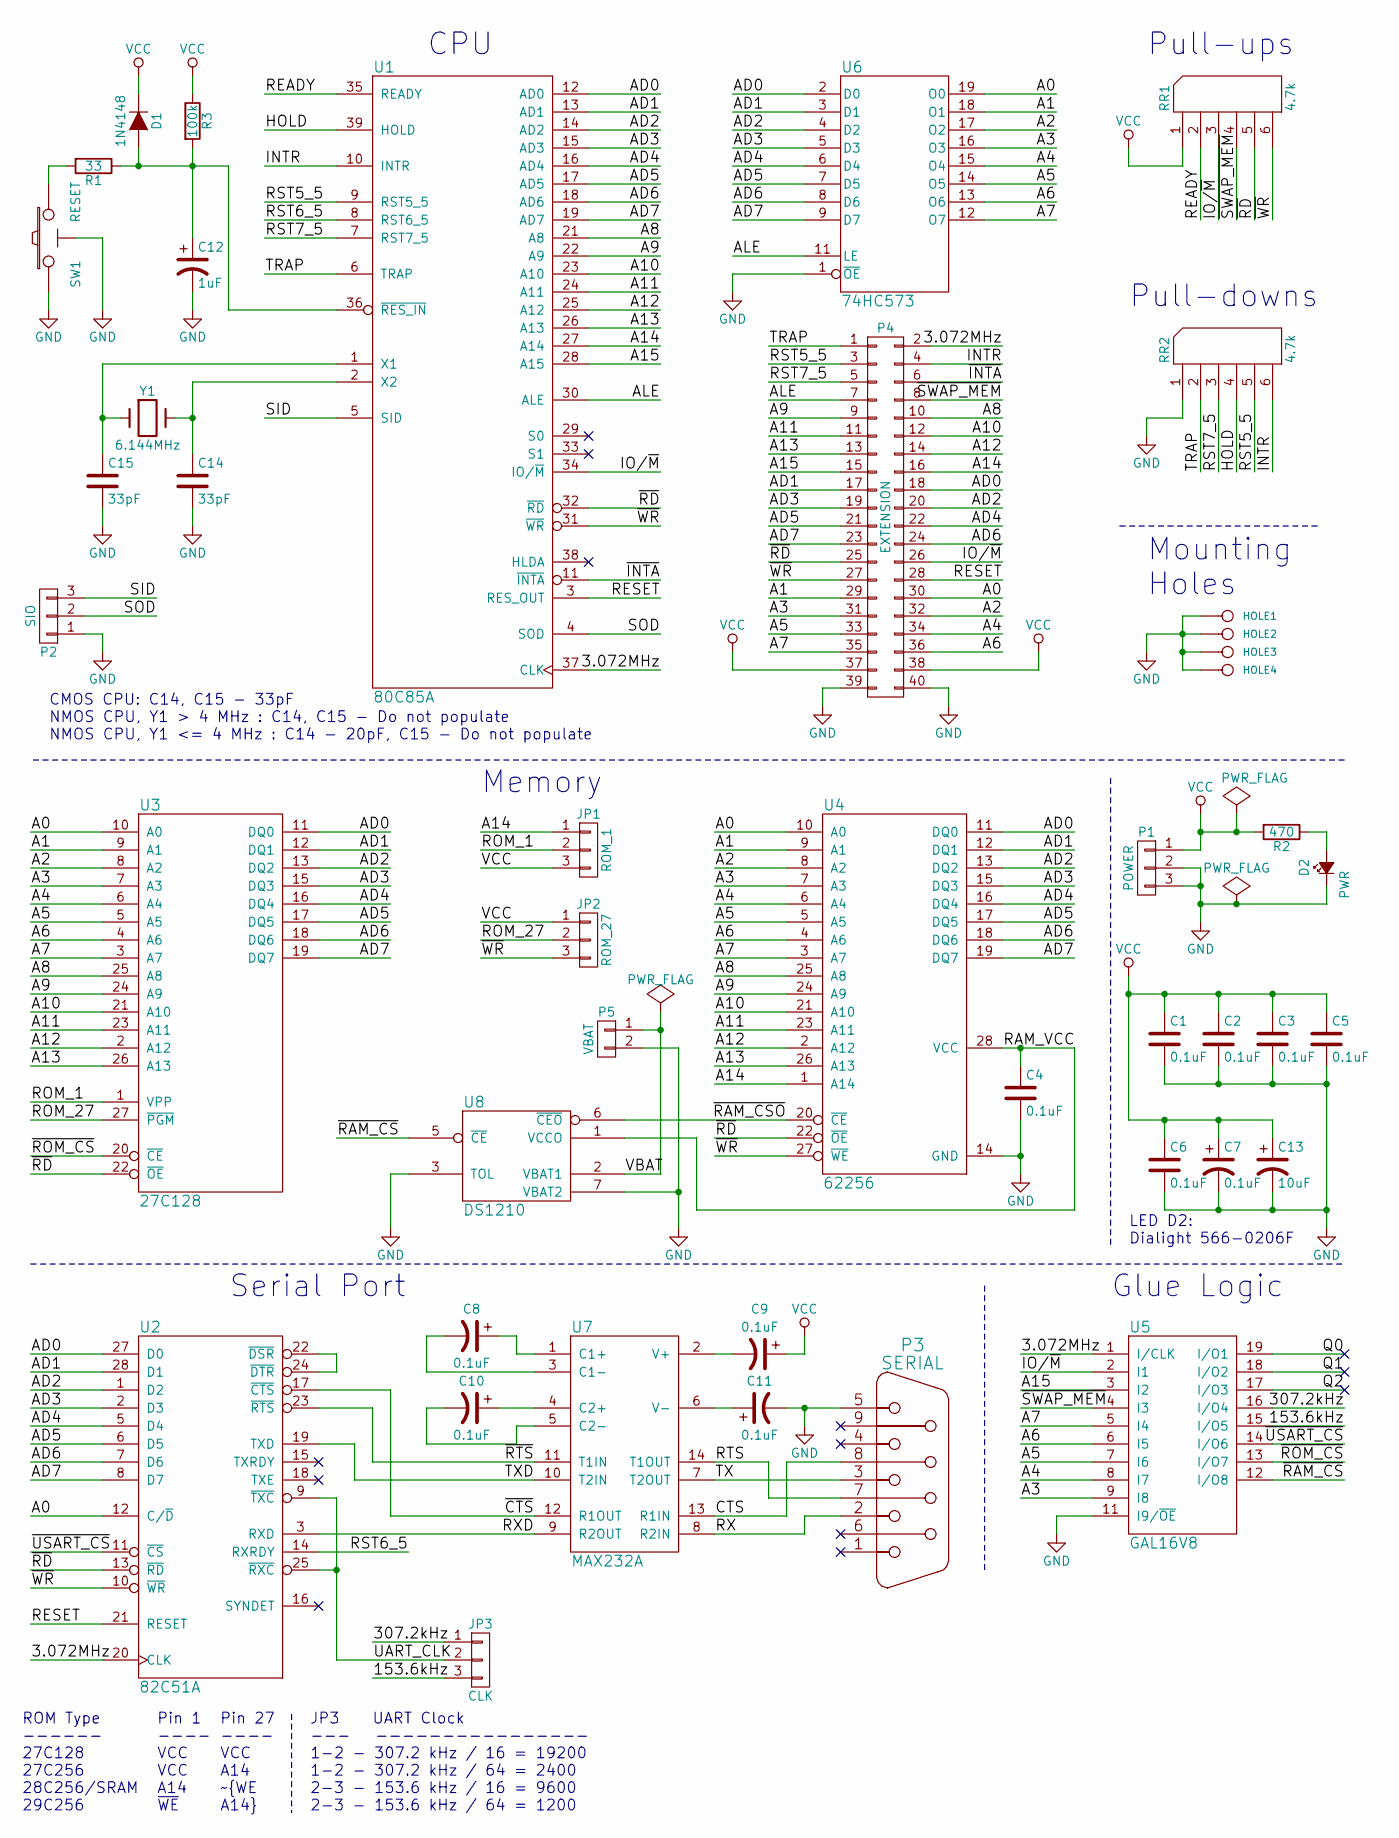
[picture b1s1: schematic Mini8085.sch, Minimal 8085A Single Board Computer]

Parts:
C1, C2, C3, C4, C5, C6: 0.1uF; Cap_Cer_508
C7, C8, C9, C10, C11: 0.1uF; Cap_Pol_508_3
C12: 1uF; Cap_Pol_508_3
C13: 10uF; Cap_Pol_508_3
C14, C15: 33pF; Cap_Cer_508
D1: 1N4148; Diode_762
D2: PWR; LED_Dialight_566-0206F
HOLE1, HOLE2, HOLE3, HOLE4: CONN_1; Hole_3mm
JP1: ROM_1; Conn_Pin_Header_3x1_2.54mm
JP2: ROM_27; Conn_Pin_Header_3x1_2.54mm
JP3: CLK; Conn_Pin_Header_3x1_2.54mm
P1: POWER; Conn_Power_Jack_Circular_Pads
P2: SIO; Conn_Pin_Header_3x1_2.54mm
P3: SERIAL; Conn_Dsub_DE9M
P4: EXTENSION; Conn_Pin_Header_20x2_2.54mm
P5: VBAT; Conn_Friction_Lock_2P_2.54mm
R1: 33; Res_762
R2: 470; Res_762
R3: 100k; Res_762
RR1, RR2: 4.7k; Conn_SIL6
SW1: RESET; Switch_Tactile_6mm_Right
U1: 80C85A; IC_DIP40_600
U2: 82C51A; IC_DIP28_600
U3: 27C128; IC_DIP28_600
U4: 62256; IC_DIP28_600
U5: GAL16V8; IC_DIP20_300
U6: 74HC573; IC_DIP20_300
U7: MAX232A; IC_DIP16_300
U8: DS1210; IC_DIP8_300
Y1: 6.144MHz; Crystal_HC-49U_Vert

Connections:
/3.072MHz: P4.2, U1.37 (CLK), U2.20 (CLK), U5.1 (I/CLK)
/153.6kHz: JP3.3, U5.15 (I/O5)
/307.2kHz: JP3.1, U5.16 (I/O4)
/A0: P4.30, U2.12 (C/~D), U3.10 (A0), U4.10 (A0), U6.19 (O0)
/A1: P4.29, U3.9 (A1), U4.9 (A1), U6.18 (O1)
/A2: P4.32, U3.8 (A2), U4.8 (A2), U6.17 (O2)
/A3: P4.31, U3.7 (A3), U4.7 (A3), U5.9 (I8), U6.16 (O3)
/A4: P4.34, U3.6 (A4), U4.6 (A4), U5.8 (I7), U6.15 (O4)
/A5: P4.33, U3.5 (A5), U4.5 (A5), U5.7 (I6), U6.14 (O5)
/A6: P4.36, U3.4 (A6), U4.4 (A6), U5.6 (I5), U6.13 (O6)
/A7: P4.35, U3.3 (A7), U4.3 (A7), U5.5 (I4), U6.12 (O7)
/A8: P4.10, U1.21 (A8), U3.25 (A8), U4.25 (A8)
/A9: P4.9, U1.22 (A9), U3.24 (A9), U4.24 (A9)
/A10: P4.12, U1.23 (A10), U3.21 (A10), U4.21 (A10)
/A11: P4.11, U1.24 (A11), U3.23 (A11), U4.23 (A11)
/A12: P4.14, U1.25 (A12), U3.2 (A12), U4.2 (A12)
/A13: P4.13, U1.26 (A13), U3.26 (A13), U4.26 (A13)
/A14: JP1.1, P4.16, U1.27 (A14), U4.1 (A14)
/A15: P4.15, U1.28 (A15), U5.3 (I2)
/AD0: P4.18, U1.12 (AD0), U2.27 (D0), U3.11 (DQ0), U4.11 (DQ0), U6.2 (D0)
/AD1: P4.17, U1.13 (AD1), U2.28 (D1), U3.12 (DQ1), U4.12 (DQ1), U6.3 (D1)
/AD2: P4.20, U1.14 (AD2), U2.1 (D2), U3.13 (DQ2), U4.13 (DQ2), U6.4 (D2)
/AD3: P4.19, U1.15 (AD3), U2.2 (D3), U3.15 (DQ3), U4.15 (DQ3), U6.5 (D3)
/AD4: P4.22, U1.16 (AD4), U2.5 (D4), U3.16 (DQ4), U4.16 (DQ4), U6.6 (D4)
/AD5: P4.21, U1.17 (AD5), U2.6 (D5), U3.17 (DQ5), U4.17 (DQ5), U6.7 (D5)
/AD6: P4.24, U1.18 (AD6), U2.7 (D6), U3.18 (DQ6), U4.18 (DQ6), U6.8 (D6)
/AD7: P4.23, U1.19 (AD7), U2.8 (D7), U3.19 (DQ7), U4.19 (DQ7), U6.9 (D7)
/ALE: P4.7, U1.30 (ALE), U6.11 (LE)
/CTS: P3.8, U7.13 (R1IN)
/HOLD: RR2.4, U1.39 (HOLD)
/INTR: P4.4, RR2.6, U1.10 (INTR)
/IO/~M: P4.26, RR1.3, U1.34 (IO/~M), U5.2 (I1)
/Q0: U5.19 (I/O1)
/Q1: U5.18 (I/O2)
/Q2: U5.17 (I/O3)
/RAM_VCC: C4.1, U4.28 (VCC), U8.1 (VCCO)
/READY: RR1.2, U1.35 (READY)
/RESET: P4.28, U1.3 (RES_OUT), U2.21 (RESET)
/ROM_1: JP1.2, U3.1 (VPP)
/ROM_27: JP2.2, U3.27 (~PGM)
/RST5_5: P4.3, RR2.5, U1.9 (RST5_5)
/RST6_5: U1.8 (RST6_5), U2.14 (RXRDY)
/RST7_5: P4.5, RR2.3, U1.7 (RST7_5)
/RTS: P3.7, U7.14 (T1OUT)
/RX: P3.2, U7.8 (R2IN)
/RXD: U2.3 (RXD), U7.9 (R2OUT)
/SID: P2.3, U1.5 (SID)
/SOD: P2.2, U1.4 (SOD)
/TRAP: P4.1, RR2.2, U1.6 (TRAP)
/TX: P3.3, U7.7 (T2OUT)
/TXD: U2.19 (TXD), U7.10 (T2IN)
/UART_CLK: JP3.2, U2.9 (~TXC), U2.25 (~RXC)
/VBAT: P5.1, U8.2 (VBAT1)
/~CTS: U2.17 (~CTS), U7.12 (R1OUT)
/~INTA: P4.6, U1.11 (~INTA)
/~RAM_CS: U5.12 (I/O8), U8.5 (~CE)
/~RAM_CSO: U4.20 (~CE), U8.6 (~CEO)
/~RD: P4.25, RR1.5, U1.32 (~RD), U2.13 (~RD), U3.22 (~OE), U4.22 (~OE)
/~ROM_CS: U3.20 (~CE), U5.13 (I/O7)
/~RTS: U2.23 (~RTS), U7.11 (T1IN)
/~SWAP_MEM: P4.8, RR1.4, U5.4 (I3)
/~USART_CS: U2.11 (~CS), U5.14 (I/O6)
/~WR: JP2.3, P4.27, RR1.6, U1.31 (~WR), U2.10 (~WR), U4.27 (~WE)
GND: C1.2, C2.2, C3.2, C4.2, C5.2, C6.2, C7.2, C11.2, C12.2, C13.2, C14.2, C15.2, D2.1 (K), HOLE1.1, HOLE2.1, HOLE3.1, HOLE4.1, P1.2, P1.3, P2.1, P3.5, P3.GND, P4.39, P4.40, P5.2, RR2.1 (COM), SW1.1, SW1.GND, U1.20 (GND), U2.4 (GND), U3.14 (GND), U4.14 (GND), U5.10 (GND), U5.11 (I9/~OE), U6.1 (~OE), U6.10 (GND), U7.15 (GND), U8.3 (TOL), U8.4 (GND), U8.7 (VBAT2)
unnamed: C8.1, U7.1 (C1+)
unnamed: C8.2, U7.3 (C1-)
unnamed: C9.2, U7.2 (V+)
unnamed: C10.1, U7.4 (C2+)
unnamed: C10.2, U7.5 (C2-)
unnamed: C11.1, U7.6 (V-)
unnamed: C12.1, D1.2 (A), R1.1, R3.2, U1.36 (~RES_IN)
unnamed: C14.1, U1.2 (X2), Y1.2
unnamed: C15.1, U1.1 (X1), Y1.1
unnamed: D2.2 (A), R2.1
unnamed: R1.2, SW1.2
unnamed: U2.22 (~DSR), U2.24 (~DTR)
VCC: C1.1, C2.1, C3.1, C5.1, C6.1, C7.1, C9.1, C13.1, D1.1 (K), JP1.3, JP2.1, P1.1, P4.37, P4.38, R2.2, R3.1, RR1.1 (COM), U1.40 (VCC), U2.26 (VCC), U3.28 (VCC), U5.20 (VCC), U6.20 (VCC), U7.16 (VCC), U8.8 (VCC)

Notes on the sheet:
ROM Type ------ 27C128 27C256 28C256/SRAM 29C256
CMOS CPU: C14, C15 - 33pF NMOS CPU, Y1 > 4 MHz : C14, C15 - Do not populate NMOS CPU, Y1 <= 4 MHz : C14 - 20pF, C15 - Do not populate
Memory
Serial Port
CPU
Pull-downs
Mounting Holes
LED D2: Dialight 566-0206F
Glue Logic
Pull-ups
JP3 UART Clock --- ---------------- 1-2 - 307.2 kHz / 16 = 19200 1-2 - 307.2 kHz / 64 = 2400 2-3 - 153.6 kHz / 16 = 9600 2-3 - 153.6 kHz / 64 = 1200
Pin 1 ---- VCC VCC A14 ~WE
Pin 27 ---- VCC A14 ~WE A14

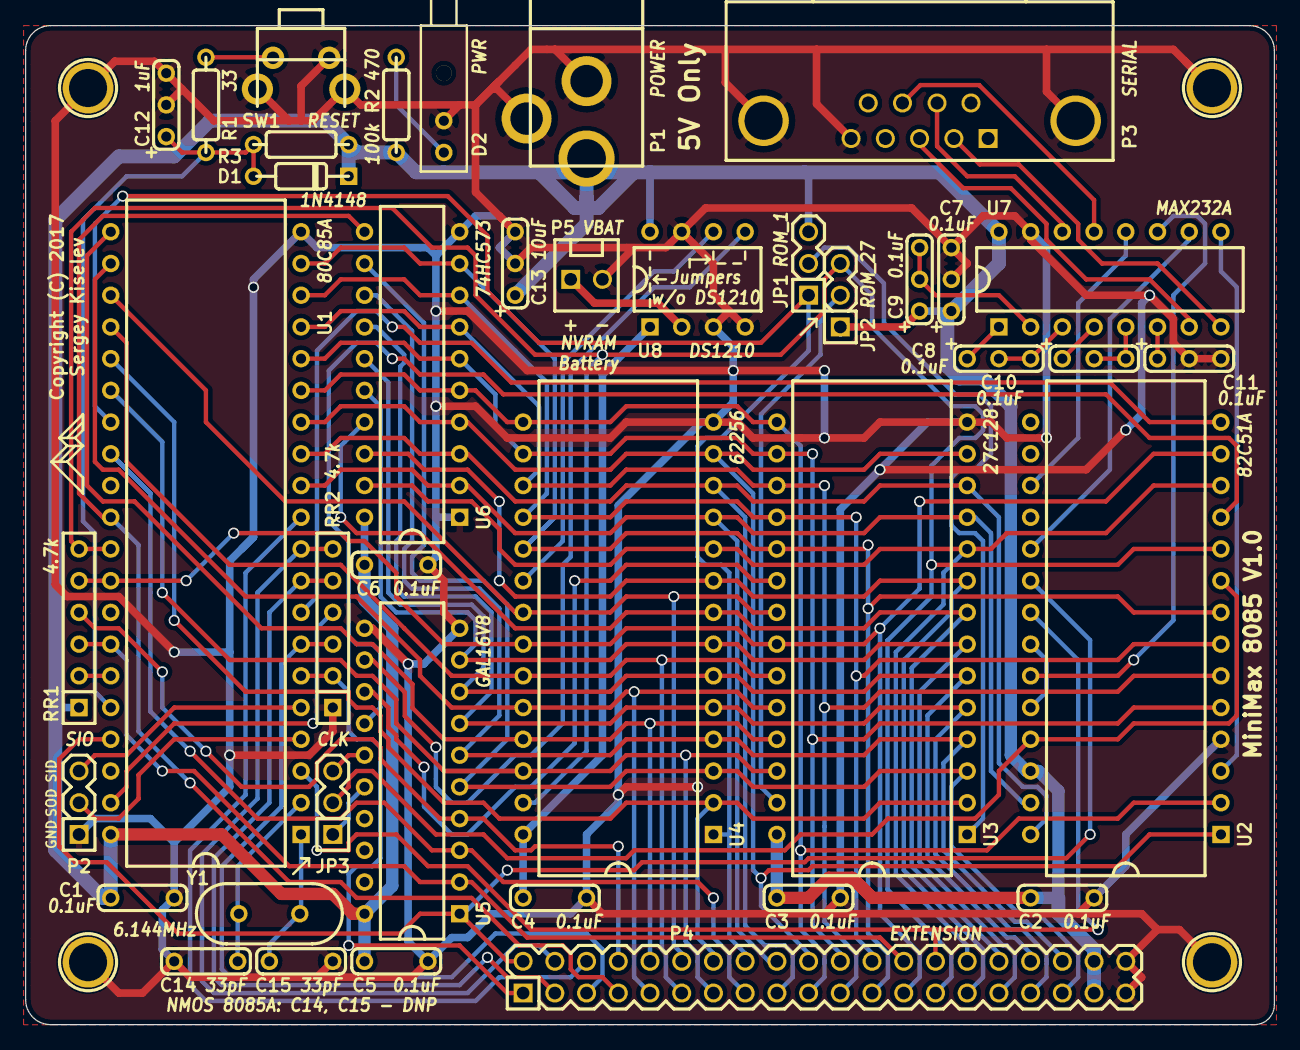
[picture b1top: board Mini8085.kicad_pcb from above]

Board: 2 copper layers, 100.0 x 80.0 mm, 44 parts (0 on the bottom side), 74 nets.

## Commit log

2020-02-10 printed_parts: Add OpenSCAD and STL files
2020-02-10 printed_parts: Create README
2020-02-10 printed_parts: Update file paths
2021-09-22 Add 8kbasic from Omen Alpha project
2021-09-22 Patch 8kbasic for AS Macro Assembler
2021-09-22 Add 8kbasic for MiniMax 8085, configured to start at 0x1800
2021-09-22 Add IMSAI 8K BASIC manual and binary for MiniMax 8085
2021-09-22 Add TINY BASIC 2.0
2021-09-22 Path TINY BASIC for AS Macro Assembler
2021-09-22 Add TINY BASIC documentation and code for MiniMax 8085
2021-09-22 Add MON85 for MiniMax 8085
2021-09-22 Add simple USART test program
2021-09-22 Add MON85 Version 1.2 original files from Roman Borik
2021-09-22 Add SPLD source and fuse maps
2021-09-22 Add CPU and EEPROM datasheets and manuals
2021-09-22 Add KiCad design files and Gerber PCB files
2021-09-22 Add README.md
2021-09-22 README: Fix obvious formatting issues and typos
2021-09-22 README: Add images
2021-09-22 README: Add links to SPLD files
2021-09-23 README: BOM: Add links to parts
2021-09-23 README: BOM: Add more part links
2021-09-23 README: BOM: Add missing part links
2021-09-23 README: Reformat tables
2021-09-23 README: Update bit rate selection notes
2021-09-23 README: Typos
2021-09-24 README: Add table of content
2021-09-24 Add ROM binary
2021-09-24 README: Add 3D Printable Enclosure information
2021-09-30 README: Add reference to Keypad and VFD Extension Board
2022-01-12 README: Add reference to MiniMax 8085 Arithmetic Processor and Extension board
2022-01-12 README: Add TOC for Arithmetic and Extension Board

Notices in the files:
KiCad/Mini8085.kicad_pcb:
Copyright (C) 2017
